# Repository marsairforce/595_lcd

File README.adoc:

= Serial shift register LCD Library for Arduino =

The serial_595_lcd library provides the software interface to use a HD44780 type parallel LCD display
through a 74HC595, so that only (3) digital output pins are required to control it.

This was inspired by those I2C or SPI LCD backpacks from Adafruit.

Only here, well, we just use a 74HC595.

The library requires (3) digital IO pins on your Arduino.

There are some assumptions for how the LCD is connected to the 74HC595, see the
schematic in the doc folder.

For more information about this library please visit us at
https://github.com/marsairforce/595_lcd

== License ==

Copyright (c) 2017 Travis Hein. All right reserved.

This library is free software; you can redistribute it and/or
modify it under the terms of the GNU Lesser General Public
License as published by the Free Software Foundation; either
version 2.1 of the License, or (at your option) any later version.

This library is distributed in the hope that it will be useful,
but WITHOUT ANY WARRANTY; without even the implied warranty of
MERCHANTABILITY or FITNESS FOR A PARTICULAR PURPOSE. See the GNU
Lesser General Public License for more details.

You should have received a copy of the GNU Lesser General Public
License along with this library; if not, write to the Free Software
Foundation, Inc., 51 Franklin St, Fifth Floor, Boston, MA 02110-1301 USA

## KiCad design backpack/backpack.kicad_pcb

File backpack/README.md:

# A LCD Backpack module using 74HC595
This is a Kicad project for a printed circuit board to place a 74HC595 on the back of a LCD display.

Board available on OSHPark: https://oshpark.com/projects/P1p8G9Nj

# BOM
All parts are available on Digikey (except the circuit board, link above..)

|Part Number | Description | Price |
|------------|-------------|------:|
|[MC74HC595ADR2GOSCT-ND](https://www.digikey.ca/product-detail/en/on-semiconductor/MC74HC595ADR2G/MC74HC595ADR2GOSCT-ND/1139727)|IC SHIFT REGISTR 8BIT 3ST 16SOIC| $0.58|
|[987-1014-1-ND](https://www.digikey.ca/product-detail/en/tt-electronics-bi/23BR10KLFTR/987-1014-1-ND/2409025)|TRIMMER 10K OHM 0.25W SMD| $1.75|
|[987-1015-1-ND](https://www.digikey.ca/product-detail/en/tt-electronics-bi/23BR1KLFTR/987-1015-1-ND/2409026)|TRIMMER 1K OHM 0.25W SMD| $1.75|
|[WM4103-ND](https://www.digikey.ca/products/en?keywords=WM4103-ND)|CONN HEADER 5POS .100 R/A TIN| $0.58|
|[OSH Park boards](https://oshpark.com/projects/P1p8G9Nj)| Pack of 3|* $2.13|

* Where the price of the board is per board. OSH Park requires you order in quantities of 3 boards, and their price is in USD, so converting and adjusting for CDN here.

So the cost to build one backpack module is about $7 CDN plus taxes. One could do better ordering bulk quantities of these components, or substituting for things on hand in your junk bin.

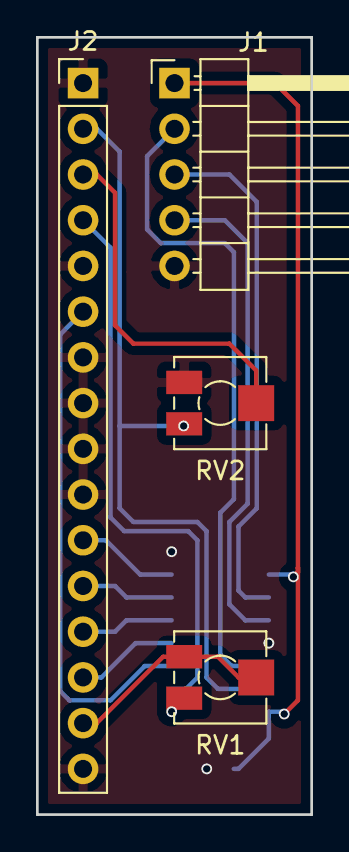
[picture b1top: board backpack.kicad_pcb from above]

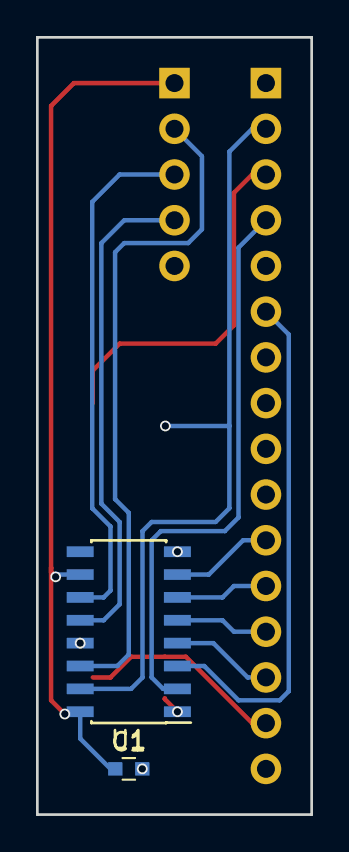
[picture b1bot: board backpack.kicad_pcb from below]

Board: 2 copper layers, 15.2 x 43.2 mm, 6 parts (2 on the bottom side), 15 nets.

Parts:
C1: 0.1uF; C_0603
J1: Conn_01x05; Pin_Header_Angled_1x05_Pitch2.54mm
J2: Conn_01x16; Pin_Header_Straight_1x16_Pitch2.54mm
RV1: 1K; Potentiometer_Trimmer_Vishay_TS53YJ
RV2: 10K; Potentiometer_Trimmer_Vishay_TS53YJ
U1: 74HC595; SOIC-16_3.9x9.9mm_Pitch1.27mm

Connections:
/D4: J2.11, U1.7
/D5: J2.12, U1.6
/D6: J2.13, U1.5
/D7: J2.14, U1.4
/E: J2.6, U1.3
/LED+: J2.15, RV1.2, RV1.3
/RCLK: J1.4, U1.12
/RS: J2.4, U1.2
/SER: J1.2, U1.14
/SRCLK: J1.3, U1.11
/VDD: J2.2, RV2.1, U1.15
/VO: J2.3, RV2.2
GND: C1.2, J1.5, J2.1, J2.5, J2.7, J2.8, J2.9, J2.10, J2.16, RV2.3, U1.8, U1.13
unnamed: RV1.1, U1.1
VCC: C1.1, J1.1, U1.10, U1.16

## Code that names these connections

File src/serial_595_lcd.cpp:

// member functions for serial_lcd

#include "LCD.h"
#include <inttypes.h>
#include <Arduino.h>

Serial_595_lcd::Serial_595_lcd(uint8_t pin_ser, uint8_t pin_srclk, uint8_t pin_rclk) {
  _m_ser   = pin_ser;
  _m_srclk = pin_srclk;
  _m_rclk  = pin_rclk;

  pinMode(_m_ser,   OUTPUT);
  pinMode(_m_srclk, OUTPUT);
  pinMode(_m_rclk,  OUTPUT);
  digitalWrite(_m_rclk, LOW);
}

// class virtual functions

void Serial_595_lcd::begin(uint8_t cols, uint8_t rows, uint8_t charsize) {
  _data.field.power=1;
  HD44780_LCD::begin(cols, rows, charsize);
  backlight();
}

void Serial_595_lcd::setBacklight(uint8_t status) {
  _data.field.backlight=status;
  port_write();
}

inline size_t Serial_595_lcd::write(uint8_t value) {
  send(value, HIGH);
  return 1;
}

void Serial_595_lcd::send(uint8_t value, boolean mode) {

  // set up RS
  _data.field.rs = mode;
  _data.field.data = 0;
  port_write();

  _data.field.en = 1;
  port_write();

  // upper 4 bits
  _data.field.data |= value  >> 4;
  port_write();

  _data.field.en = 0;
  port_write();
  delayMicroseconds(1);

  _data.field.en = 1;
  port_write();

  // lower 4 bits
  _data.field.data = 0;
  _data.field.data |= value;
  port_write();

  _data.field.en = 0;
  port_write();

  // _data.field.rs = 0; // turn off data and control pins
  // port_write();
}

void Serial_595_lcd::write4bits(uint8_t data) {
  // see the write timing diagram
  _data.field.rs = 0; // rs is always 0. we only write nibbles for reset sequence.
  _data.field.data = 0;
  _data.field.en = 1;
  port_write();

  // set the data. Make sure just the lower 8 bits get changed.
  _data.field.data |= data ;
  port_write();

  // toggle E. This causes the data to be written to the LCD.
  _data.field.en = 0;
  port_write();
}

void Serial_595_lcd::powerOn() {
  _data.field.power=1;
  port_write();
  initialize();
  backlight();
}

void Serial_595_lcd::powerOff() {
  _data.raw = 0;
  port_write();
}

// low level function
void Serial_595_lcd::port_write() {
  shiftOut(_m_ser, _m_srclk, LSBFIRST, _data.raw);
  digitalWrite(_m_rclk, HIGH);
  digitalWrite(_m_ser, LOW);
  digitalWrite(_m_rclk, LOW);
}



// void Serial_595_lcd::set_e() {
//   _data.field.en = 1;
//   port_write();
// }

// void Serial_595_lcd::clear_e() {
//   _data.field.en = 0;
//   port_write();
// }

// void Serial_595_lcd::toggle_e() {
//   _data.field.en = 1;
//   port_write();
//   delayMicroseconds(50);
//   _data.field.en = 0;
//   port_write();
// }


// void Serial_595_lcd::reset_sequence() {
//   // https://electronics.stackexchange.com/questions/102245/hd44780-initialization-for-4-bit-mode
//   // http://web.alfredstate.edu/faculty/weimandn/lcd/lcd_initialization/lcd_initialization_index.html
//   // http://www.farnell.com/datasheets/50586.pdf

//   write4bits(0x3);  // function set [ 0 0 1 DL N 0 * * ] ; DL=1 for 8 bit mode, 0 for 4 bit mode ; N=1 for 16:1 mux, 8 for 8:1
// //  delayMicroseconds(5000); // was 4500
//   ;
//   toggle_e(); // toggle E 2 more times (pass the function set value again twice more basically)
// //  delayMicroseconds(100); // was 100

//   toggle_e();
// //  delayMicroseconds(100);

//   write4bits(0x2); // Function set (Set interface to 4 bits)
// //  delayMicroseconds(100);

//   _data.field.data = 0;
//   port_write();
// }

// void Serial_595_lcd::initialize() {
//   reset_sequence();
//   send(0x2C, false); // function set (2 lines, 5x11 font)
//   send(0x08, false); // display off, cursor off, blink off
//   send(0x01, false); // clear screen & return cursor home
//   send(0x06, false); // inc cursor to the right when writing and don't shift the screen
//   send(0x0C, false); // turn display on
// }

// void Serial_595_lcd::set_dram_address(unsigned char address) {
//   send(0x80 + (address & 0x7F), false);
// }

/**
     * The devices provide a 7 bit DRAM address
     * Internally there are 40 character columns, even if the display does not physically have this many columns
     * The row offsets are not consecutive starting points.
     * e.g. for 40 characters, this only uses 0x00-0x27 (0-39)for the first line
     * but the second line in the dram address starts at 0x40-0x67
     * what about those 25 (0x19) bytes from 0x28-0x39?
     *
     * To make it more complicated, 4 line display modules that have less than 40 characters per line
     * e.g. like these 20x4 modles I have http://www.newhavendisplay.com/specs/NHD-0420DZ-NSW-BBW.pdf
     * use the not visible DRAM address positions from line 1 are mapped to display line 3.
     * I guess this means we can not do the scroll display
     *
     * The set dram address command is 0x80, plus the memory offset.
     * so we want to convert the input of (x,y) to the linear value
     * that satisfies this mess.
     */
// void Serial_595_lcd::gotoxy(unsigned char x, unsigned char y) {
//   int offset = 0;
//   if (x > (_m_cols - 1)) {
//     // error
//     return;
//   }
//   if (y > (_m_rows - 1)) {
//     // error
//     return;
//   }
//   if ( y == 1 || y == 3 ) {
//     offset += 0x40;
//   }
//   if (y == 2 || y == 3 ) {
//     offset += 20;
//   }
//   offset += x;
//   set_dram_address(offset);
// }

// void Serial_595_lcd::puts(char *str) {
//   for (int i = 0; str[i] != 0; i++) {
//     send(str[i], true);
//   }
//   _data.field.data = 0;
//   _data.field.rs = 0;
//   port_write();
// }

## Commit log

2018-03-15 set up project folder
2018-03-15 rename because libraries can not start with a number.
2018-03-15 first set of features
    this was what I needed for now.
2018-03-15 create an example sketch
2018-03-15 set serial control lines low after write operation.
    add timing diagram of serial and control data.
2018-03-15 udpate documentation
2018-03-15 restore accidentally deleted image
2018-03-16 optimize the write sequences and timings.
2018-03-16 adjust initializing timings to allow older displays to work.
2018-03-17 bugfix row boundary check for gotoxy.
2018-03-17 Design a small circuit board for the electronics.
    I created an LCD backback board on OSHPark
2018-03-17 update documentation
2018-03-17 create a bill of materials
2018-03-17 add board images
2018-03-19 conditional defines around button macros
    so we can have other libraries define these later and not have problems with symbol declared already.
2018-03-19 start to convert c functions to c++ class member functions.
2018-03-26 bugfix the write byte function. This got broken and was not allowing the display to work.
2018-03-26 v2 snapshot
2018-03-26 bugfix display not working
2018-03-26 bugfix v1 example.
2018-03-26 remove v1 api
2018-03-28 allow screen dimensions to be set. start to build screen buffer functions.
2018-03-30 start to organize an abstraction of LCD functions from specific type of serial interface.
2018-03-30 Building LCD class functions for parallel mode, based on the Arduino LiquidCrystal library.
    So far the timing for the signals on the scope look wrong.
2018-03-30 it helps if we don't break the pinmode
2018-03-30 now that a parallel mode display works on a breadboard, lets try to get this 1602 lcd keypad shield to work.
    Created another example that makes use of the keypad shield LCD and buttons.
2018-03-30 start support for Adafruit I2C backpack
2018-03-30 fix the adafruit i2c interface mode
2018-03-30 convert member properties to define constants to reduce memory footprint.
2018-03-30 refactor lcd constants out of header file. we never use these.
2018-03-30 Create support for PCF8574 type serial backpacks. Add docuementation.
    Here we are trying something new, using union and struct to represent the bit fields instead of needing to do our own bit manipulation and masking.
2018-03-31 update serial 595 implementation to be compatible with the class API.
    the only main change is we need our begin() to power on the LCD. The other devices do not have a power control interface.
2018-03-31 update documentation.
2018-04-01 Support SPI mode for Adafruit LCD backpack.
    Refactoring backlight method into the LCD class.
    Adding isBacklight() so the backlight state can be queried.
2018-04-01 organize a class for the lcd keypad shield. This is a piece of hardware. We don't have a choice what IO pins it uses. So then why do we have to make the user specify this. Attempt to use a pointer to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
2018-04-01 clean up stale timing diagrams
2018-04-01 first attempt at using a screen buffer.
    Here we use it on the example LCD keypad shield.
2018-04-01 try to improve serial mode driver.
    so far its not working. something about the ordering of the bits is not right from the bit field?
2018-04-25 add power control functions
2018-04-25 update documentation and license
2018-04-25 add support for USIWire
    For ATTiny devices, which do not have a hardware I2C port we can use this very nice software implementation of I2C that uses the USI hardware.
2018-05-14 simplify the screen buffer features.
    for now just use a static buffer size of 20x4
    and disable the windowing abilities.
    it would seem dynamically allocating the memory and using string copy functions was causing
    us issues where memory would be corrupted, or reading from the buffer would fetch more than
    it should. Remember the LCD screen is not a simple null terminated string. It is just an
    array of characters.
